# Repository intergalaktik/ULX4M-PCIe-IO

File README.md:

# ULX4M-PCIe-IO
NLnet funded PCIe board that can hold ULX4M-LD 

## PCIexpress-KiCad templates
PCI Express™ libraries and templates for KiCad
Made using guidelines from PCI Express™ Card Electromechanical Specification Rev. 1.1

### Contents
**Template used:**
* x4 cards: full size, half length, low profile

**FPGA reference boards:**

* https://github.com/gatecat/TrellisBoard
* https://github.com/enjoy-digital/litex-acorn-baseboard

**Symbols:**
* x4
* Bracket

**Footprints:**
* x4 with multiple card outlines
* Full height bracket (with 3D model)

## Comfirmed working

- [x] 12V
- [x] 5V
- [x] 3.3V
- [x] DVI
- [x] WS2812 diodes
- [x] FTDI ove HAT

## Partially working

- [ ] PCIe loopback is working if TX/RX is bricked on boad edge, but not with PCIe externsion on CM4 IO board

## Not tested

- [ ] GPIOs
- [ ] SPDIFs
- [ ] SFPs
- [ ] PCIe comm to PC

# Not working

- [ ] OLED - pins are not connected on ULX4M
- [ ] 1x / 4x PCIe selection - it is not connected

### License
This documentation describes Open Hardware and is licensed under the CERN OHL v.1.2.

You may redistribute and modify this documentation under the terms of the CERN OHL v.1.2. (http://ohwr.org/cernohl). This documentation is distributed WITHOUT ANY EXPRESS OR IMPLIED WARRANTY, INCLUDING OF MERCHANTABILITY, SATISFACTORY QUALITY AND FITNESS FOR A PARTICULAR PURPOSE. Please see the CERN OHL v.1.2 for applicable conditions.

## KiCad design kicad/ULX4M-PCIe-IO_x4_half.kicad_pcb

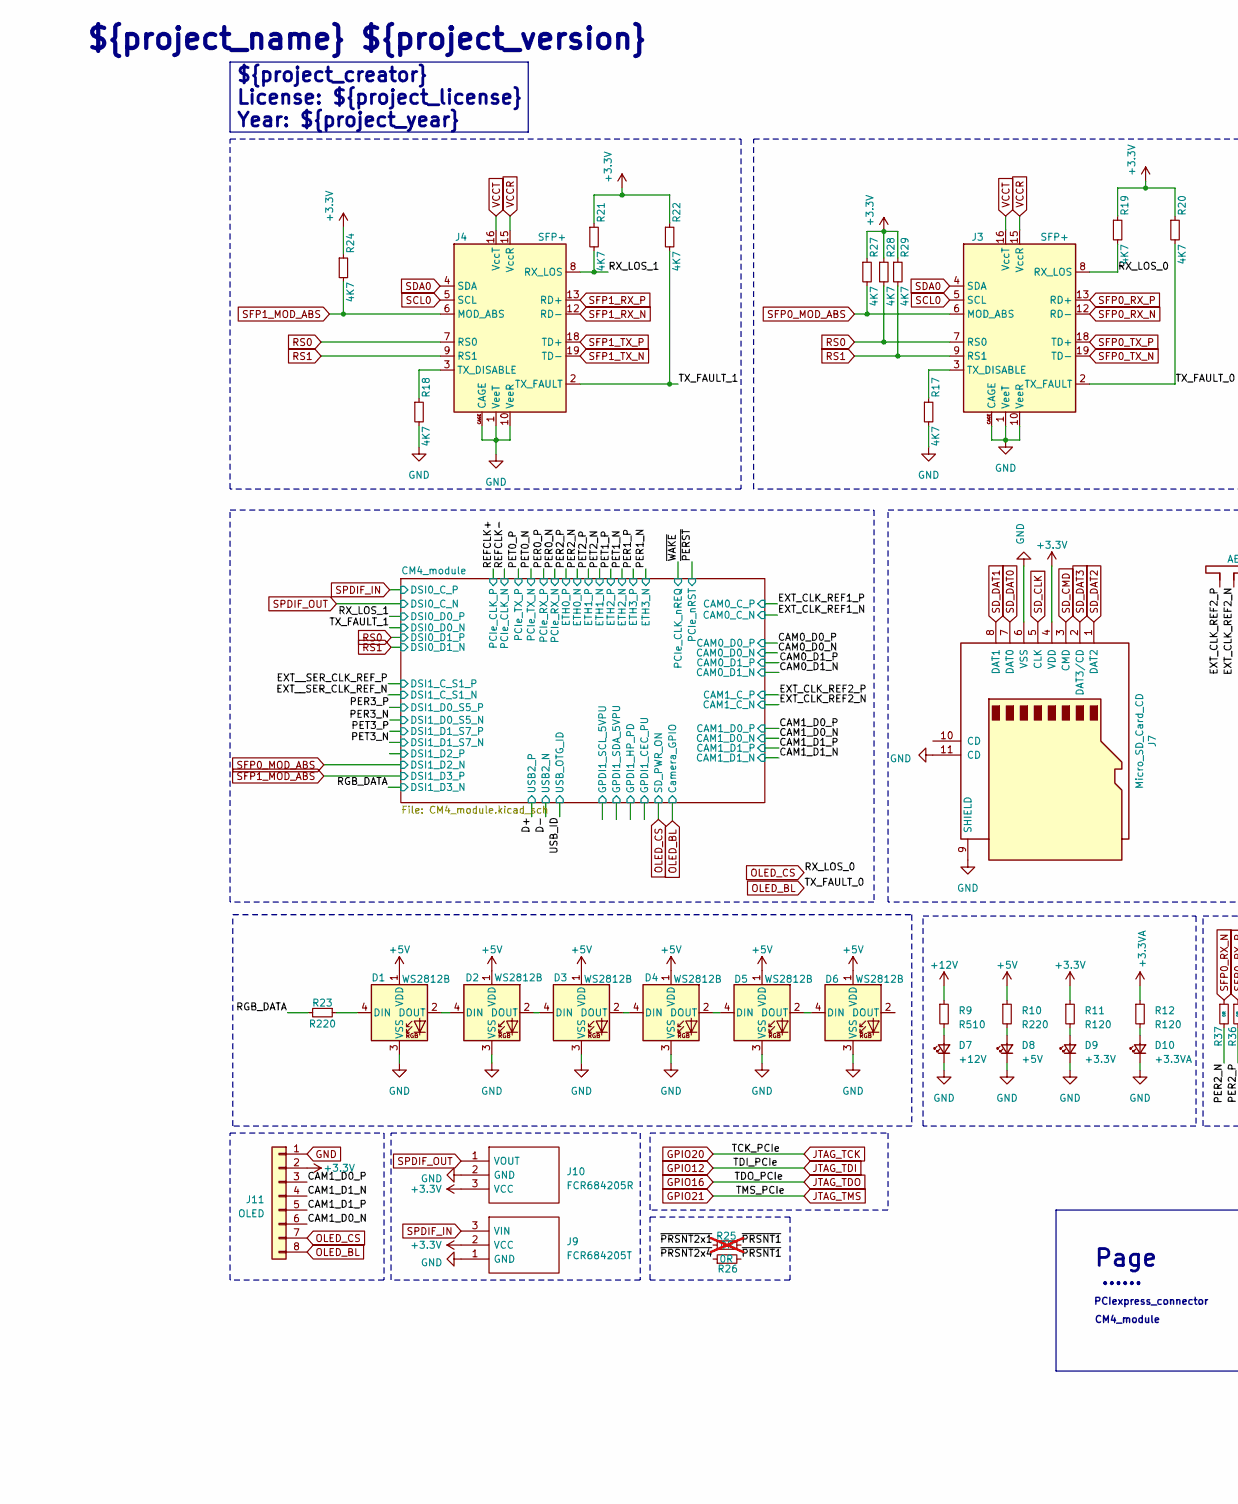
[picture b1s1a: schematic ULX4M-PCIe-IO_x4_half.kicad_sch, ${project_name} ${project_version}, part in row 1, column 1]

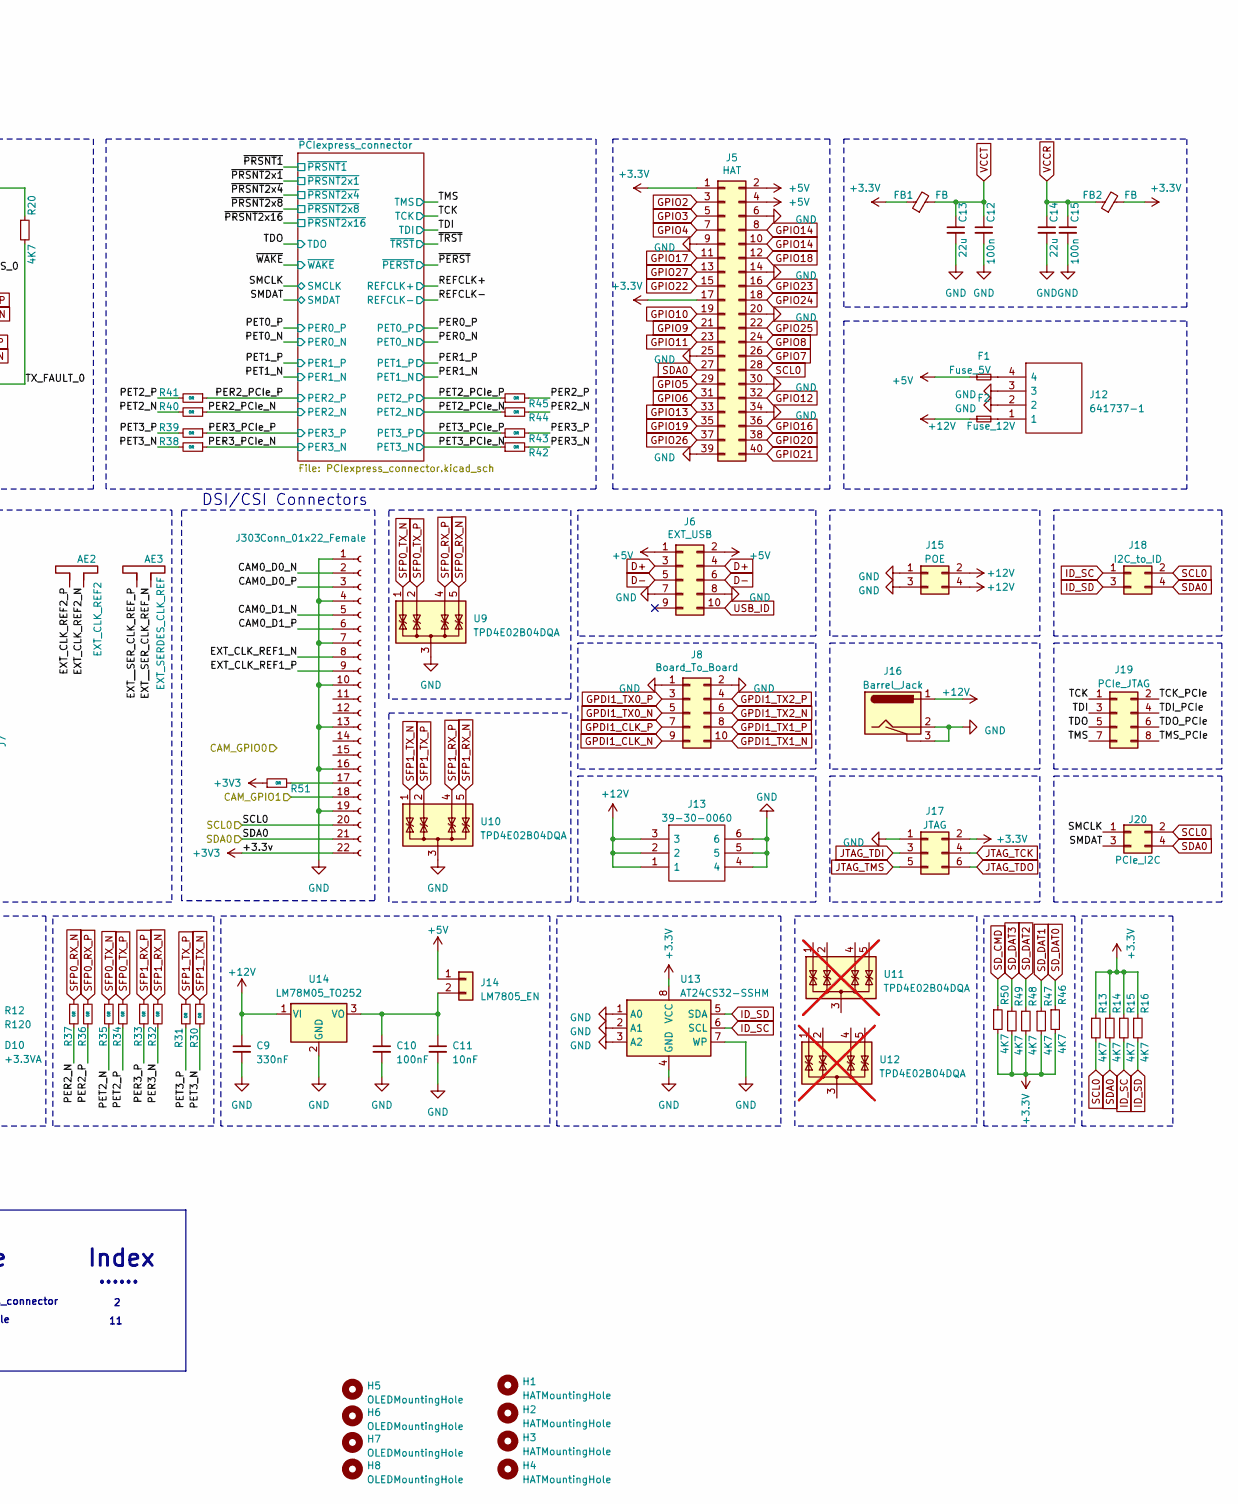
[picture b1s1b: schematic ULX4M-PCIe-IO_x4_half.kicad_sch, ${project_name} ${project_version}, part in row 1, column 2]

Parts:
AE2: EXT_CLK_REF2; SMA_Amphenol_132291-12_Vertical
AE3: EXT_SERDES_CLK_REF; SMA_Amphenol_132291-12_Vertical
C9: 330nF; C_0603_1608Metric
C10: 100nF; C_0603_1608Metric
C11: 10nF; C_0603_1608Metric
C12, C15: 100n; C_0603_1608Metric
C13, C14: 22u; C_0603_1608Metric
D1, D2, D3, D4, D5, D6: WS2812B; LED_WS2812B_PLCC4_5.0x5.0mm_P3.2mm
D7: +12V; LED_0603_1608Metric
D8: +5V; LED_0603_1608Metric
D9: +3.3V; LED_0603_1608Metric
D10: +3.3VA; LED_0603_1608Metric
F1: Fuse_5V; Fuse_1206_3216Metric
F2: Fuse_12V; Fuse_1206_3216Metric
FB1, FB2: FB; L_0603_1608Metric
H1, H2, H3, H4: HATMountingHole; MountingHole_3.2mm_M3
H5, H6, H7, H8: OLEDMountingHole; MountingHole_3.2mm_M3
J3, J4: SFP+; Connector_SFP_and_Cage
J5: HAT; PinHeader_2x20_P2.54mm_Vertical
J6: EXT_USB; PinHeader_2x05_P2.54mm_Vertical
J7: Micro_SD_Card_CD; microSD_HC_Molex_104031-0811
J8: Board_To_Board; PinSocket_2x06_P2.54mm_Horizontal
J9: FCR684205T; Manufacturer_Part_Number FCR684205T
J10: FCR684205R; Manufacturer_Part_Number FCR684205R
J11: OLED; PinHeader_1x08_P2.54mm_Vertical
J12: 641737-1; Mouser Part Number 571-6417371
J13: 39-30-0060; 39-30-Y060; Mouser Part Number 538-39-30-0060
J14: LM7805_EN; PinHeader_1x02_P2.54mm_Vertical
J15: POE; PinHeader_2x02_P2.54mm_Vertical
J16: Barrel_Jack; BarrelJack_Horizontal
J17: JTAG; PinHeader_2x03_P2.54mm_Vertical
J18: I2C_to_ID; PinHeader_2x02_P2.54mm_Vertical
J19: PCIe_JTAG; PinHeader_2x04_P2.54mm_Vertical
J20: PCIe_I2C; PinHeader_2x02_P2.54mm_Vertical
J303: Conn_01x22_Female; Hirose_FH12-22S-0.5SH_1x22-1MP_P0.50mm_Horizontal; Part Description 22 Position FFC, FPC Connector Contacts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; LCSC C597981
R9: R510; R_0603_1608Metric
R10, R23: R220; R_0603_1608Metric
R11, R12: R120; R_0603_1608Metric
R13, R14, R15, R16, R17, R18, R19, R20, R21, R22, R24, R27, R28, R29, R46, R47, R48, R49, R50: 4K7; R_0603_1608Metric
R25: 0R; R_0603_1608Metric; not fitted
R26, R30, R31, R32, R33, R34, R35, R36, R37, R38, R39, R40, R41, R42, R43, R44, R45, R51: 0R; R_0603_1608Metric
U9, U10: TPD4E02B04DQA; USON-10_2.5x1.0mm_P0.5mm
U11, U12: TPD4E02B04DQA; USON-10_2.5x1.0mm_P0.5mm; not fitted
U13: AT24CS32-SSHM; SOIC-8_3.9x4.9mm_P1.27mm
U14: LM78M05_TO252; TO-252-2

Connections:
+3.3V: FB1.1, FB2.2, J5.1, J5.17, J7.4 (VDD), J9.2 (VCC), J10.3 (VCC), J11.2, J17.2, R11.1, R13.1, R14.1, R15.1, R16.1, R19.1, R20.1, R21.1, R22.1, R24.1, R27.1, R28.1, R29.1, R46.2, R47.2, R48.2, R49.2, R50.2, U13.8 (VCC); also elsewhere on the board
+3.3VA: R12.1; also elsewhere on the board
+3V3: J303.22, R51.1; also elsewhere on the board
+5V: D1.1 (VDD), D2.1 (VDD), D3.1 (VDD), D4.1 (VDD), D5.1 (VDD), D6.1 (VDD), F1.1, J5.2, J5.4, J6.1, J6.2, J14.1, R10.1; also elsewhere on the board
+12V: C9.1, F2.1, J13.1, J13.2, J13.3, J15.2, J15.4, J16.1, R9.1, U14.1 (VI); also elsewhere on the board
/CAM0_D0_N: J303.2; also elsewhere on the board
/CAM0_D0_P: J303.3; also elsewhere on the board
/CAM0_D1_N: J303.5; also elsewhere on the board
/CAM0_D1_P: J303.6; also elsewhere on the board
/CAM1_D0_N: J11.6; also elsewhere on the board
/CAM1_D0_P: J11.3; also elsewhere on the board
/CAM1_D1_N: J11.4; also elsewhere on the board
/CAM1_D1_P: J11.5; also elsewhere on the board
/CAM_GPIO1: J303.18
/EXT_CLK_REF1_N: J303.8; also elsewhere on the board
/EXT_CLK_REF1_P: J303.9; also elsewhere on the board
/EXT_CLK_REF2_N: AE2.2; also elsewhere on the board
/EXT_CLK_REF2_P: AE2.1; also elsewhere on the board
/EXT__SER_CLK_REF_N: AE3.2; also elsewhere on the board
/EXT__SER_CLK_REF_P: AE3.1; also elsewhere on the board
/PER2_N: R37.2, R44.2; also elsewhere on the board
/PER2_P: R36.2, R45.2; also elsewhere on the board
/PER2_PCIe_N: R40.1; also elsewhere on the board
/PER2_PCIe_P: R41.1; also elsewhere on the board
/PER3_N: R32.2, R42.2; also elsewhere on the board
/PER3_P: R33.2, R43.2; also elsewhere on the board
/PER3_PCIe_N: R38.1; also elsewhere on the board
/PER3_PCIe_P: R39.1; also elsewhere on the board
/PET2_N: R35.2, R40.2; also elsewhere on the board
/PET2_P: R34.2, R41.2; also elsewhere on the board
/PET2_PCIe_N: R44.1; also elsewhere on the board
/PET2_PCIe_P: R45.1; also elsewhere on the board
/PET3_N: R30.2, R38.2; also elsewhere on the board
/PET3_P: R31.2, R39.2; also elsewhere on the board
/PET3_PCIe_N: R42.1; also elsewhere on the board
/PET3_PCIe_P: R43.1; also elsewhere on the board
/RGB_DATA: R23.2; also elsewhere on the board
/RX_LOS_1: J4.8 (RX_LOS), R21.2; also elsewhere on the board
/SMCLK: J20.1; also elsewhere on the board
/SMDAT: J20.3; also elsewhere on the board
/TCK: J19.1; also elsewhere on the board
/TDI: J19.3; also elsewhere on the board
/TDO: J19.5; also elsewhere on the board
/TMS: J19.7; also elsewhere on the board
/TX_FAULT_1: J4.2 (TX_FAULT), R22.2; also elsewhere on the board
/~PRSNT1: R25.2, R26.2; also elsewhere on the board
/~PRSNT2x1: R25.1; also elsewhere on the board
/~PRSNT2x4: R26.1; also elsewhere on the board
D+: J6.3, J6.4; also elsewhere on the board
D-: J6.5, J6.6; also elsewhere on the board
GND: C9.2, C10.2, C11.2, C12.2, C13.2, C14.2, C15.2, D1.3 (VSS), D2.3 (VSS), D3.3 (VSS), D4.3 (VSS), D5.3 (VSS), D6.3 (VSS), D7.1 (K), D8.1 (K), D9.1 (K), D10.1 (K), J3.1 (VeeT), J3.10 (VeeR), J3.11 (VeeR), J3.14 (VeeR), J3.17 (VeeT), J3.20 (VeeT), J3.CAGE, J4.1 (VeeT), J4.10 (VeeR), J4.11 (VeeR), J4.14 (VeeR), J4.17 (VeeT), J4.20 (VeeT), J4.CAGE, J5.6, J5.9, J5.14, J5.20, J5.25, J5.30, J5.34, J5.39, J6.7, J6.8, J7.6 (VSS), J7.9 (SHIELD), J7.11 (CD), J8.1, J8.2, J9.1 (GND), J10.2 (GND), J11.1, J12.2, J12.3, J13.4, J13.5, J13.6, J15.1, J15.3, J16.2, J16.3, J17.1, J303.1, J303.4, J303.7, J303.10, J303.13, J303.16, J303.19, R17.2, R18.2, U9.3 (G), U9.8 (G), U10.3 (G), U10.8 (G), U13.1 (A0), U13.2 (A1), U13.3 (A2), U13.4 (GND), U13.7 (WP), U14.2 (GND); also elsewhere on the board
GPDI1_CLK_N: J8.9; also elsewhere on the board
GPDI1_CLK_P: J8.7; also elsewhere on the board
GPDI1_TX0_N: J8.5; also elsewhere on the board
GPDI1_TX0_P: J8.3; also elsewhere on the board
GPDI1_TX1_N: J8.10; also elsewhere on the board
GPDI1_TX1_P: J8.8; also elsewhere on the board
GPDI1_TX2_N: J8.6; also elsewhere on the board
GPDI1_TX2_P: J8.4; also elsewhere on the board
GPIO2: J5.3; also elsewhere on the board
GPIO3: J5.5; also elsewhere on the board
GPIO4: J5.7; also elsewhere on the board
GPIO5: J5.29; also elsewhere on the board
GPIO6: J5.31; also elsewhere on the board
GPIO7: J5.26; also elsewhere on the board
GPIO8: J5.24; also elsewhere on the board
GPIO9: J5.21; also elsewhere on the board
GPIO10: J5.19; also elsewhere on the board
GPIO11: J5.23; also elsewhere on the board
GPIO12: J5.32, J17.3, J19.4; also elsewhere on the board
GPIO13: J5.33; also elsewhere on the board
GPIO14: J5.8, J5.10; also elsewhere on the board
GPIO16: J5.36, J17.6, J19.6; also elsewhere on the board
GPIO17: J5.11; also elsewhere on the board
GPIO18: J5.12; also elsewhere on the board
GPIO19: J5.35; also elsewhere on the board
GPIO20: J5.38, J17.4, J19.2; also elsewhere on the board
GPIO21: J5.40, J17.5, J19.8; also elsewhere on the board
GPIO22: J5.15; also elsewhere on the board
GPIO23: J5.16; also elsewhere on the board
GPIO24: J5.18; also elsewhere on the board
GPIO25: J5.22; also elsewhere on the board
GPIO26: J5.37; also elsewhere on the board
GPIO27: J5.13; also elsewhere on the board
ID_SC: J18.1, R15.2, U13.6 (SCL); also elsewhere on the board
ID_SD: J18.3, R16.2, U13.5 (SDA); also elsewhere on the board
unnamed: D1.4 (DIN), R23.1
unnamed: D1.2 (DOUT), D2.4 (DIN)
unnamed: D2.2 (DOUT), D3.4 (DIN)
unnamed: D3.2 (DOUT), D4.4 (DIN)
unnamed: D4.2 (DOUT), D5.4 (DIN)
unnamed: D5.2 (DOUT), D6.4 (DIN)
unnamed: D7.2 (A), R9.2
unnamed: D8.2 (A), R10.2
unnamed: D9.2 (A), R11.2
unnamed: D10.2 (A), R12.2
unnamed: F1.2, J12.4
unnamed: F2.2, J12.1
unnamed: J3.3 (TX_DISABLE), R17.1
unnamed: J4.3 (TX_DISABLE), R18.1
unnamed: C10.1, C11.1, J14.2, U14.3 (VO)
unnamed: J303.17, R51.2
unnamed: U11.3 (G), U11.8 (G)
unnamed: U12.3 (G), U12.8 (G)
OLED_BL: J3.2 (TX_FAULT), J11.8, R20.2; also elsewhere on the board
OLED_CS: J3.8 (RX_LOS), J11.7, R19.2; also elsewhere on the board
RS0: J3.7 (RS0), J4.7 (RS0), R28.2; also elsewhere on the board
RS1: J3.9 (RS1), J4.9 (RS1), R29.2; also elsewhere on the board
SCL0: J3.5 (SCL), J4.5 (SCL), J5.28, J18.2, J20.2, J303.20, R13.2; also elsewhere on the board
SDA0: J3.4 (SDA), J4.4 (SDA), J5.27, J18.4, J20.4, J303.21, R14.2; also elsewhere on the board
SD_CLK: J7.5 (CLK); also elsewhere on the board
SD_CMD: J7.3 (CMD), R50.1; also elsewhere on the board
SD_DAT0: J7.7 (DAT0), R46.1; also elsewhere on the board
SD_DAT1: J7.8 (DAT1), R47.1; also elsewhere on the board
SD_DAT2: J7.1 (DAT2), R48.1; also elsewhere on the board
SD_DAT3: J7.2 (DAT3/CD), R49.1; also elsewhere on the board
SFP0_MOD_ABS: J3.6 (MOD_ABS), R27.2; also elsewhere on the board
SFP0_RX_N: J3.12 (RD-), R37.1, U9.5 (IO4)
SFP0_RX_P: J3.13 (RD+), R36.1, U9.4 (IO3)
SFP0_TX_N: J3.19 (TD-), R35.1, U9.1 (IO1)
SFP0_TX_P: J3.18 (TD+), R34.1, U9.2 (IO2)
SFP1_MOD_ABS: J4.6 (MOD_ABS), R24.2; also elsewhere on the board
SFP1_RX_N: J4.12 (RD-), R32.1, U10.5 (IO4)
SFP1_RX_P: J4.13 (RD+), R33.1, U10.4 (IO3)
SFP1_TX_N: J4.19 (TD-), R30.1, U10.1 (IO1)
SFP1_TX_P: J4.18 (TD+), R31.1, U10.2 (IO2)
SPDIF_IN: J9.3 (VIN); also elsewhere on the board
SPDIF_OUT: J10.1 (VOUT); also elsewhere on the board
USB_ID: J6.10; also elsewhere on the board
VCCR: C14.1, C15.1, FB2.1, J3.15 (VccR), J4.15 (VccR)
VCCT: C12.1, C13.1, FB1.2, J3.16 (VccT), J4.16 (VccT)

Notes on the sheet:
Page
Index
......
DSI/CSI Connectors
${project_creator} License: ${project_license} Year: ${project_year}
PCIexpress_connector
${project_name} ${project_version}
CM4_module

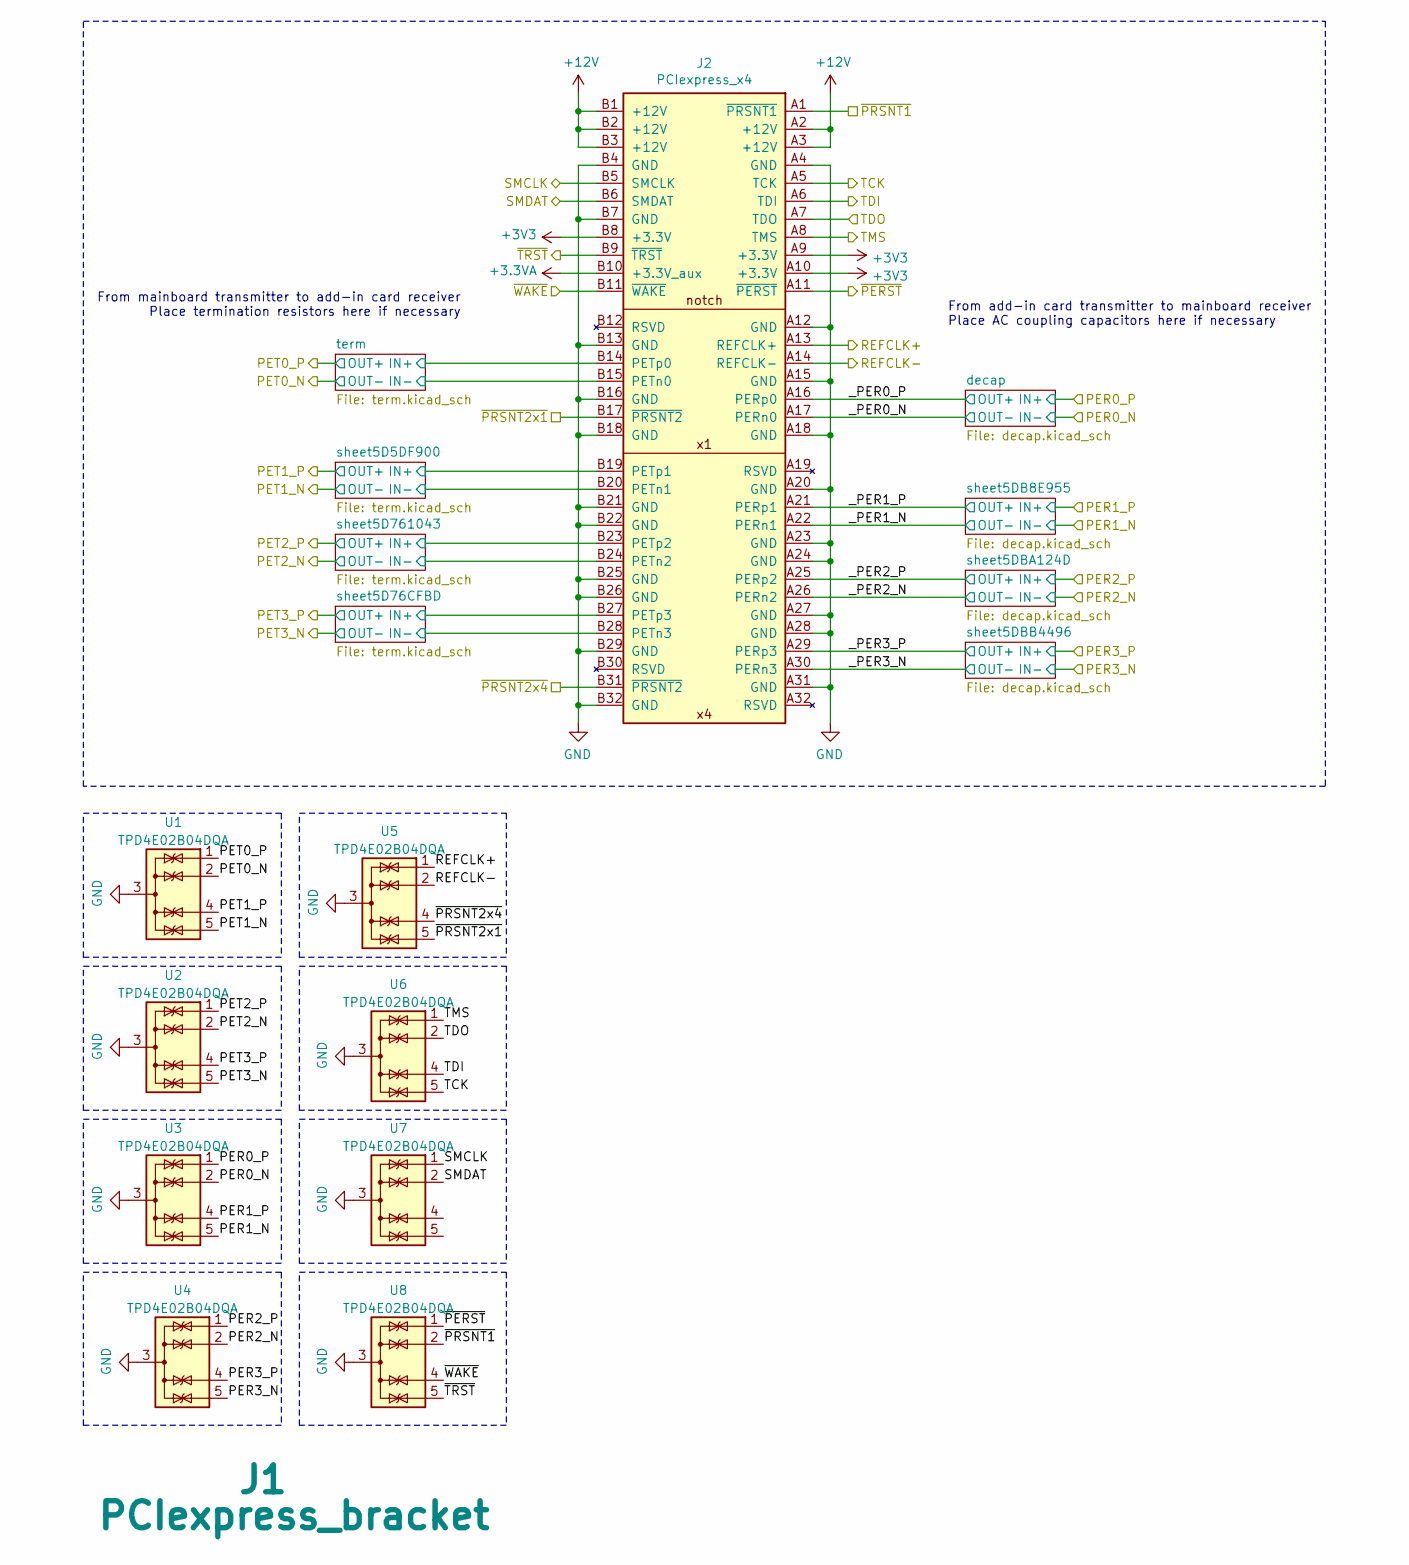
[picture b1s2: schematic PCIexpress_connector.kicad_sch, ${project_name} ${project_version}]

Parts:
J1: PCIexpress_bracket; PCIexpress_bracket_full
J2: PCIexpress_x4
U1, U2, U3, U4, U5, U6, U7, U8: TPD4E02B04DQA; USON-10_2.5x1.0mm_P0.5mm

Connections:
+3.3VA: J2.B10 (+3.3V_aux); also elsewhere on the board
+3V3: J2.A9 (+3.3V), J2.A10 (+3.3V), J2.B8 (+3.3V); also elsewhere on the board
+12V: J2.A2 (+12V), J2.A3 (+12V), J2.B1 (+12V), J2.B2 (+12V), J2.B3 (+12V); also elsewhere on the board
/PCIexpress_connector/_PER0_N: J2.A17 (PERn0); also elsewhere on the board
/PCIexpress_connector/_PER0_P: J2.A16 (PERp0); also elsewhere on the board
/PCIexpress_connector/_PER1_N: J2.A22 (PERn1); also elsewhere on the board
/PCIexpress_connector/_PER1_P: J2.A21 (PERp1); also elsewhere on the board
/PCIexpress_connector/_PER2_N: J2.A26 (PERn2); also elsewhere on the board
/PCIexpress_connector/_PER2_P: J2.A25 (PERp2); also elsewhere on the board
/PCIexpress_connector/_PER3_N: J2.A30 (PERn3); also elsewhere on the board
/PCIexpress_connector/_PER3_P: J2.A29 (PERp3); also elsewhere on the board
/PER0_N: J2.B15 (PETn0), U1.2 (IO2); also elsewhere on the board
/PER0_P: J2.B14 (PETp0), U1.1 (IO1); also elsewhere on the board
/PER1_N: J2.B20 (PETn1), U1.5 (IO4); also elsewhere on the board
/PER1_P: J2.B19 (PETp1), U1.4 (IO3); also elsewhere on the board
/PER2_PCIe_N: U4.2 (IO2); also elsewhere on the board
/PER2_PCIe_P: U4.1 (IO1); also elsewhere on the board
/PER3_PCIe_N: U4.5 (IO4); also elsewhere on the board
/PER3_PCIe_P: U4.4 (IO3); also elsewhere on the board
/PET0_N: U3.2 (IO2); also elsewhere on the board
/PET0_P: U3.1 (IO1); also elsewhere on the board
/PET1_N: U3.5 (IO4); also elsewhere on the board
/PET1_P: U3.4 (IO3); also elsewhere on the board
/PET2_PCIe_N: J2.B24 (PETn2), U2.2 (IO2); also elsewhere on the board
/PET2_PCIe_P: J2.B23 (PETp2), U2.1 (IO1); also elsewhere on the board
/PET3_PCIe_N: J2.B28 (PETn3), U2.5 (IO4); also elsewhere on the board
/PET3_PCIe_P: J2.B27 (PETp3), U2.4 (IO3); also elsewhere on the board
/REFCLK+: J2.A13 (REFCLK+), U5.1 (IO1); also elsewhere on the board
/REFCLK-: J2.A14 (REFCLK-), U5.2 (IO2); also elsewhere on the board
/SMCLK: J2.B5 (SMCLK), U7.1 (IO1); also elsewhere on the board
/SMDAT: J2.B6 (SMDAT), U7.2 (IO2); also elsewhere on the board
/TCK: J2.A5 (TCK), U6.5 (IO4); also elsewhere on the board
/TDI: J2.A6 (TDI), U6.4 (IO3); also elsewhere on the board
/TDO: J2.A7 (TDO), U6.2 (IO2); also elsewhere on the board
/TMS: J2.A8 (TMS), U6.1 (IO1); also elsewhere on the board
/~PERST: J2.A11 (~PERST), U8.1 (IO1); also elsewhere on the board
/~PRSNT1: J2.A1 (~PRSNT1), U8.2 (IO2); also elsewhere on the board
/~PRSNT2x1: J2.B17 (~PRSNT2), U5.5 (IO4); also elsewhere on the board
/~PRSNT2x4: J2.B31 (~PRSNT2), U5.4 (IO3); also elsewhere on the board
/~TRST: J2.B9 (~TRST), U8.5 (IO4)
/~WAKE: J2.B11 (~WAKE), U8.4 (IO3); also elsewhere on the board
GND: J2.A4 (GND), J2.A12 (GND), J2.A15 (GND), J2.A18 (GND), J2.A20 (GND), J2.A23 (GND), J2.A24 (GND), J2.A27 (GND), J2.A28 (GND), J2.A31 (GND), J2.B4 (GND), J2.B7 (GND), J2.B13 (GND), J2.B16 (GND), J2.B18 (GND), J2.B21 (GND), J2.B22 (GND), J2.B25 (GND), J2.B26 (GND), J2.B29 (GND), J2.B32 (GND), U1.3 (G), U1.8 (G), U2.3 (G), U2.8 (G), U3.3 (G), U3.8 (G), U4.3 (G), U4.8 (G), U5.3 (G), U5.8 (G), U6.3 (G), U6.8 (G), U7.3 (G), U7.8 (G), U8.3 (G), U8.8 (G); also elsewhere on the board

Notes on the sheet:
From mainboard transmitter to add-in card receiver Place termination resistors here if necessary
From add-in card transmitter to mainboard receiver Place AC coupling capacitors here if necessary

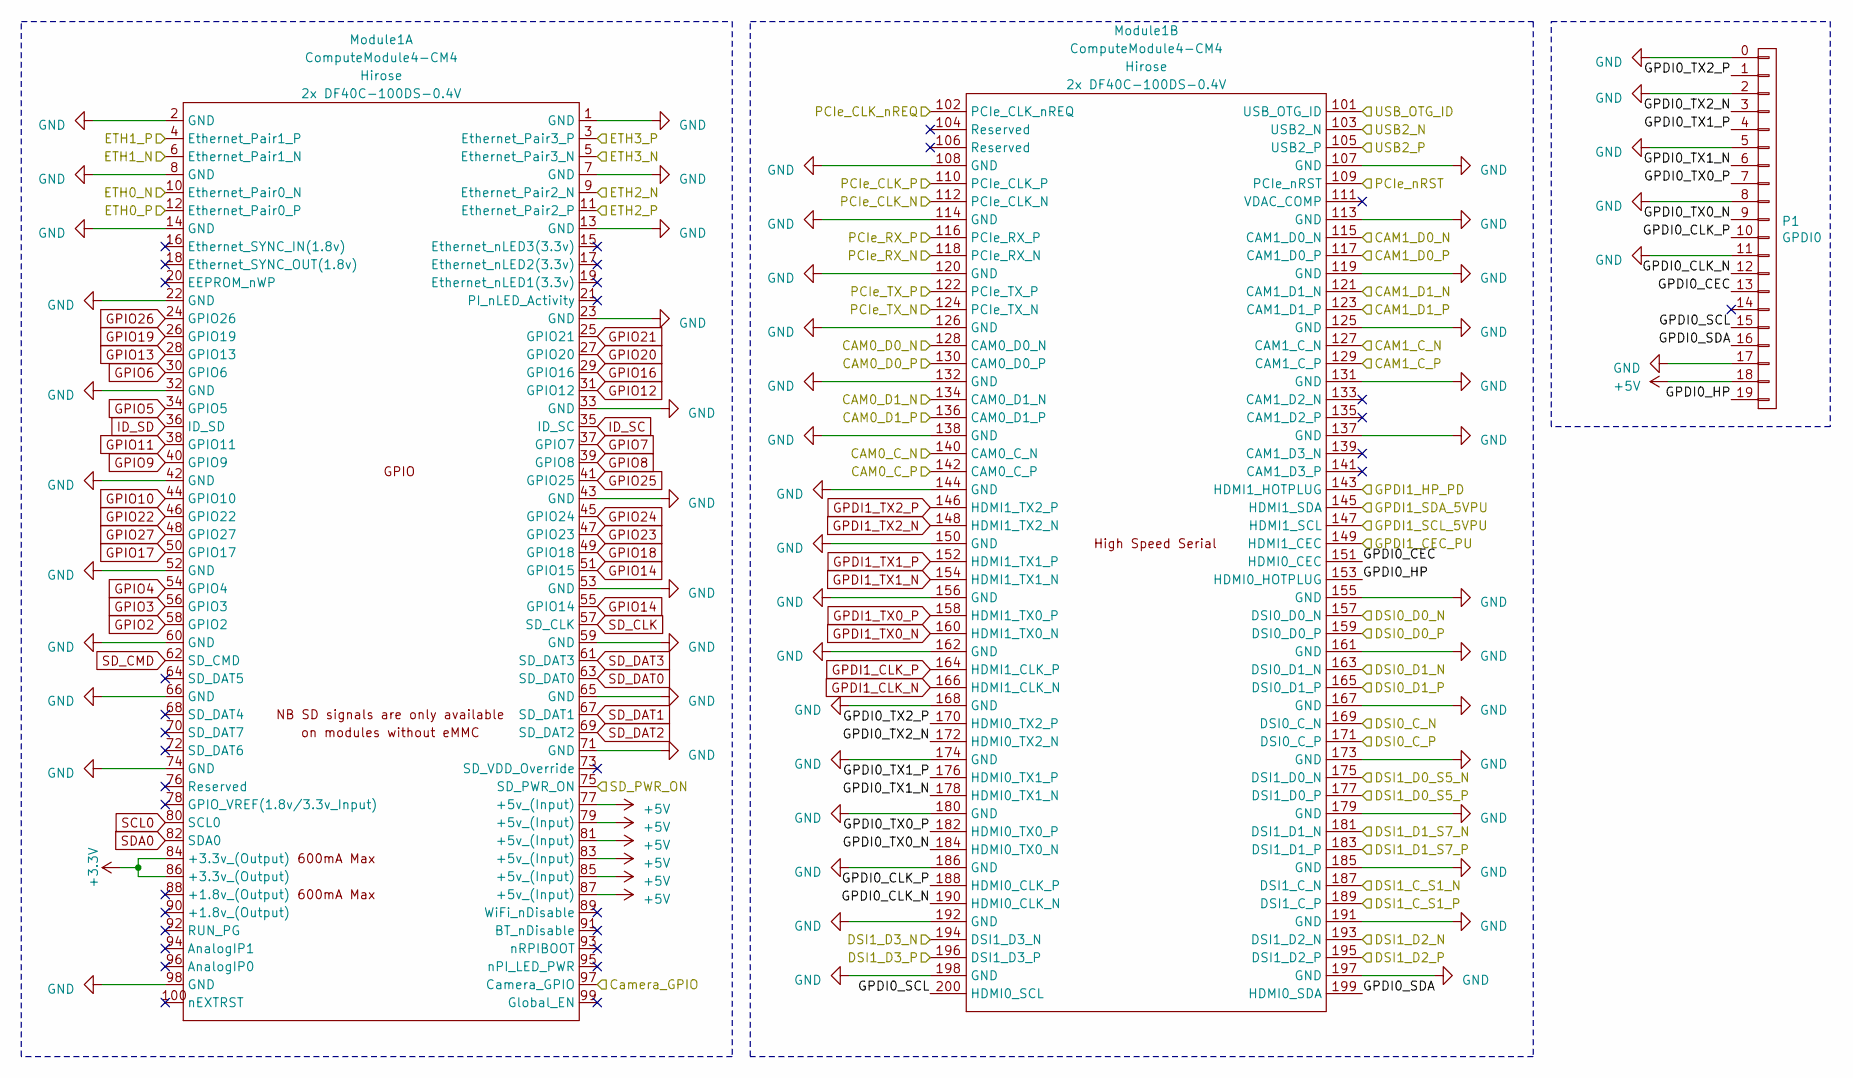
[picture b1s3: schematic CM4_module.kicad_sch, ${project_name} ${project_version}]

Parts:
Module1: ComputeModule4-CM4; Raspberry-Pi-4-Compute-Module
P1: GPDI0; CONN-10029449-111RLF

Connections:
+3.3V: Module1.84 (+3.3v_(Output)), Module1.86 (+3.3v_(Output)); also elsewhere on the board
+5V: Module1.77 (+5v_(Input)), Module1.79 (+5v_(Input)), Module1.81 (+5v_(Input)), Module1.83 (+5v_(Input)), Module1.85 (+5v_(Input)), Module1.87 (+5v_(Input)), P1.18; also elsewhere on the board
/CAM0_D0_N: Module1.128 (CAM0_D0_N); also elsewhere on the board
/CAM0_D0_P: Module1.130 (CAM0_D0_P); also elsewhere on the board
/CAM0_D1_N: Module1.134 (CAM0_D1_N); also elsewhere on the board
/CAM0_D1_P: Module1.136 (CAM0_D1_P); also elsewhere on the board
/CAM1_D0_N: Module1.115 (CAM1_D0_N); also elsewhere on the board
/CAM1_D0_P: Module1.117 (CAM1_D0_P); also elsewhere on the board
/CAM1_D1_N: Module1.121 (CAM1_D1_N); also elsewhere on the board
/CAM1_D1_P: Module1.123 (CAM1_D1_P); also elsewhere on the board
/CM4_module/DSI1_D2_P: Module1.195 (DSI1_D2_P)
/CM4_module/GPDI0_CEC: Module1.151 (HDMI0_CEC), P1.13
/CM4_module/GPDI0_CLK_N: Module1.190 (HDMI0_CLK_N), P1.12
/CM4_module/GPDI0_CLK_P: Module1.188 (HDMI0_CLK_P), P1.10
/CM4_module/GPDI0_HP: Module1.153 (HDMI0_HOTPLUG), P1.19
/CM4_module/GPDI0_SCL: Module1.200 (HDMI0_SCL), P1.15
/CM4_module/GPDI0_SDA: Module1.199 (HDMI0_SDA), P1.16
/CM4_module/GPDI0_TX0_N: Module1.184 (HDMI0_TX0_N), P1.9
/CM4_module/GPDI0_TX0_P: Module1.182 (HDMI0_TX0_P), P1.7
/CM4_module/GPDI0_TX1_N: Module1.178 (HDMI0_TX1_N), P1.6
/CM4_module/GPDI0_TX1_P: Module1.176 (HDMI0_TX1_P), P1.4
/CM4_module/GPDI0_TX2_N: Module1.172 (HDMI0_TX2_N), P1.3
/CM4_module/GPDI0_TX2_P: Module1.170 (HDMI0_TX2_P), P1.1
/CM4_module/GPDI1_CEC_PU: Module1.149 (HDMI1_CEC)
/CM4_module/GPDI1_HP_PD: Module1.143 (HDMI1_HOTPLUG)
/CM4_module/GPDI1_SCL_5VPU: Module1.147 (HDMI1_SCL)
/CM4_module/GPDI1_SDA_5VPU: Module1.145 (HDMI1_SDA)
/EXT_CLK_REF1_N: Module1.140 (CAM0_C_N); also elsewhere on the board
/EXT_CLK_REF1_P: Module1.142 (CAM0_C_P); also elsewhere on the board
/EXT_CLK_REF2_N: Module1.127 (CAM1_C_N); also elsewhere on the board
/EXT_CLK_REF2_P: Module1.129 (CAM1_C_P); also elsewhere on the board
/EXT__SER_CLK_REF_N: Module1.187 (DSI1_C_N); also elsewhere on the board
/EXT__SER_CLK_REF_P: Module1.189 (DSI1_C_P); also elsewhere on the board
/PER0_N: Module1.118 (PCIe_RX_N); also elsewhere on the board
/PER0_P: Module1.116 (PCIe_RX_P); also elsewhere on the board
/PER1_N: Module1.5 (Ethernet_Pair3_N); also elsewhere on the board
/PER1_P: Module1.3 (Ethernet_Pair3_P); also elsewhere on the board
/PER2_N: Module1.10 (Ethernet_Pair0_N); also elsewhere on the board
/PER2_P: Module1.12 (Ethernet_Pair0_P); also elsewhere on the board
/PER3_N: Module1.175 (DSI1_D0_N); also elsewhere on the board
/PER3_P: Module1.177 (DSI1_D0_P); also elsewhere on the board
/PET0_N: Module1.124 (PCIe_TX_N); also elsewhere on the board
/PET0_P: Module1.122 (PCIe_TX_P); also elsewhere on the board
/PET1_N: Module1.9 (Ethernet_Pair2_N); also elsewhere on the board
/PET1_P: Module1.11 (Ethernet_Pair2_P); also elsewhere on the board
/PET2_N: Module1.6 (Ethernet_Pair1_N); also elsewhere on the board
/PET2_P: Module1.4 (Ethernet_Pair1_P); also elsewhere on the board
/PET3_N: Module1.181 (DSI1_D1_N); also elsewhere on the board
/PET3_P: Module1.183 (DSI1_D1_P); also elsewhere on the board
/REFCLK+: Module1.110 (PCIe_CLK_P); also elsewhere on the board
/REFCLK-: Module1.112 (PCIe_CLK_N); also elsewhere on the board
/RGB_DATA: Module1.194 (DSI1_D3_N); also elsewhere on the board
/RX_LOS_1: Module1.159 (DSI0_D0_P); also elsewhere on the board
/TX_FAULT_1: Module1.157 (DSI0_D0_N); also elsewhere on the board
/~PERST: Module1.109 (PCIe_nRST); also elsewhere on the board
/~WAKE: Module1.102 (PCIe_CLK_nREQ); also elsewhere on the board
D+: Module1.105 (USB2_P); also elsewhere on the board
D-: Module1.103 (USB2_N); also elsewhere on the board
GND: Module1.1 (GND), Module1.2 (GND), Module1.7 (GND), Module1.8 (GND), Module1.13 (GND), Module1.14 (GND), Module1.22 (GND), Module1.23 (GND), Module1.32 (GND), Module1.33 (GND), Module1.42 (GND), Module1.43 (GND), Module1.52 (GND), Module1.53 (GND), Module1.59 (GND), Module1.60 (GND), Module1.65 (GND), Module1.66 (GND), Module1.71 (GND), Module1.74 (GND), Module1.98 (GND), Module1.107 (GND), Module1.108 (GND), Module1.113 (GND), Module1.114 (GND), Module1.119 (GND), Module1.120 (GND), Module1.125 (GND), Module1.126 (GND), Module1.131 (GND), Module1.132 (GND), Module1.137 (GND), Module1.138 (GND), Module1.144 (GND), Module1.150 (GND), Module1.155 (GND), Module1.156 (GND), Module1.161 (GND), Module1.162 (GND), Module1.167 (GND), Module1.168 (GND), Module1.173 (GND), Module1.174 (GND), Module1.179 (GND), Module1.180 (GND), Module1.185 (GND), Module1.186 (GND), Module1.191 (GND), Module1.192 (GND), Module1.197 (GND), Module1.198 (GND), P1.0, P1.2, P1.5, P1.8, P1.11, P1.17; also elsewhere on the board
GPDI1_CLK_N: Module1.166 (HDMI1_CLK_N); also elsewhere on the board
GPDI1_CLK_P: Module1.164 (HDMI1_CLK_P); also elsewhere on the board
GPDI1_TX0_N: Module1.160 (HDMI1_TX0_N); also elsewhere on the board
GPDI1_TX0_P: Module1.158 (HDMI1_TX0_P); also elsewhere on the board
GPDI1_TX1_N: Module1.154 (HDMI1_TX1_N); also elsewhere on the board
GPDI1_TX1_P: Module1.152 (HDMI1_TX1_P); also elsewhere on the board
GPDI1_TX2_N: Module1.148 (HDMI1_TX2_N); also elsewhere on the board
GPDI1_TX2_P: Module1.146 (HDMI1_TX2_P); also elsewhere on the board
GPIO2: Module1.58 (GPIO2); also elsewhere on the board
GPIO3: Module1.56 (GPIO3); also elsewhere on the board
GPIO4: Module1.54 (GPIO4); also elsewhere on the board
GPIO5: Module1.34 (GPIO5); also elsewhere on the board
GPIO6: Module1.30 (GPIO6); also elsewhere on the board
GPIO7: Module1.37 (GPIO7); also elsewhere on the board
GPIO8: Module1.39 (GPIO8); also elsewhere on the board
GPIO9: Module1.40 (GPIO9); also elsewhere on the board
GPIO10: Module1.44 (GPIO10); also elsewhere on the board
GPIO11: Module1.38 (GPIO11); also elsewhere on the board
GPIO12: Module1.31 (GPIO12); also elsewhere on the board
GPIO13: Module1.28 (GPIO13); also elsewhere on the board
GPIO14: Module1.51 (GPIO15), Module1.55 (GPIO14); also elsewhere on the board
GPIO16: Module1.29 (GPIO16); also elsewhere on the board
GPIO17: Module1.50 (GPIO17); also elsewhere on the board
GPIO18: Module1.49 (GPIO18); also elsewhere on the board
GPIO19: Module1.26 (GPIO19); also elsewhere on the board
GPIO20: Module1.27 (GPIO20); also elsewhere on the board
GPIO21: Module1.25 (GPIO21); also elsewhere on the board
GPIO22: Module1.46 (GPIO22); also elsewhere on the board
GPIO23: Module1.47 (GPIO23); also elsewhere on the board
GPIO24: Module1.45 (GPIO24); also elsewhere on the board
GPIO25: Module1.41 (GPIO25); also elsewhere on the board
GPIO26: Module1.24 (GPIO26); also elsewhere on the board
GPIO27: Module1.48 (GPIO27); also elsewhere on the board
ID_SC: Module1.35 (ID_SC); also elsewhere on the board
ID_SD: Module1.36 (ID_SD); also elsewhere on the board
OLED_BL: Module1.97 (Camera_GPIO); also elsewhere on the board
OLED_CS: Module1.75 (SD_PWR_ON); also elsewhere on the board
RS0: Module1.165 (DSI0_D1_P); also elsewhere on the board
RS1: Module1.163 (DSI0_D1_N); also elsewhere on the board
SCL0: Module1.80 (SCL0); also elsewhere on the board
SDA0: Module1.82 (SDA0); also elsewhere on the board
SD_CLK: Module1.57 (SD_CLK); also elsewhere on the board
SD_CMD: Module1.62 (SD_CMD); also elsewhere on the board
SD_DAT0: Module1.63 (SD_DAT0); also elsewhere on the board
SD_DAT1: Module1.67 (SD_DAT1); also elsewhere on the board
SD_DAT2: Module1.69 (SD_DAT2); also elsewhere on the board
SD_DAT3: Module1.61 (SD_DAT3); also elsewhere on the board
SFP0_MOD_ABS: Module1.193 (DSI1_D2_N); also elsewhere on the board
SFP1_MOD_ABS: Module1.196 (DSI1_D3_P); also elsewhere on the board
SPDIF_IN: Module1.171 (DSI0_C_P); also elsewhere on the board
SPDIF_OUT: Module1.169 (DSI0_C_N); also elsewhere on the board
USB_ID: Module1.101 (USB_OTG_ID); also elsewhere on the board

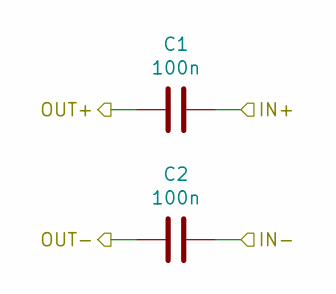
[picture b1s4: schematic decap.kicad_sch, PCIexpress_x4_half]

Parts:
C1, C2: 100n; C_0603_1608Metric

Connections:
/PCIexpress_connector/_PER0_N: C2.1; also elsewhere on the board
/PCIexpress_connector/_PER0_P: C1.2; also elsewhere on the board
/PET0_N: C2.2; also elsewhere on the board
/PET0_P: C1.1; also elsewhere on the board

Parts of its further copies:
C3, C4, C5, C6, C7, C8: 100n; C_0603_1608Metric

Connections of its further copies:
/PCIexpress_connector/_PER1_N: C4.1; also elsewhere on the board
/PCIexpress_connector/_PER1_P: C3.2; also elsewhere on the board
/PCIexpress_connector/_PER2_N: C6.1; also elsewhere on the board
/PCIexpress_connector/_PER2_P: C5.2; also elsewhere on the board
/PCIexpress_connector/_PER3_N: C8.1; also elsewhere on the board
/PCIexpress_connector/_PER3_P: C7.2; also elsewhere on the board
/PER2_PCIe_N: C6.2; also elsewhere on the board
/PER2_PCIe_P: C5.1; also elsewhere on the board
/PER3_PCIe_N: C8.2; also elsewhere on the board
/PER3_PCIe_P: C7.1; also elsewhere on the board
/PET1_N: C4.2; also elsewhere on the board
/PET1_P: C3.1; also elsewhere on the board

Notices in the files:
parts and their libraries:
project_license: CERN-OHL-S v2
